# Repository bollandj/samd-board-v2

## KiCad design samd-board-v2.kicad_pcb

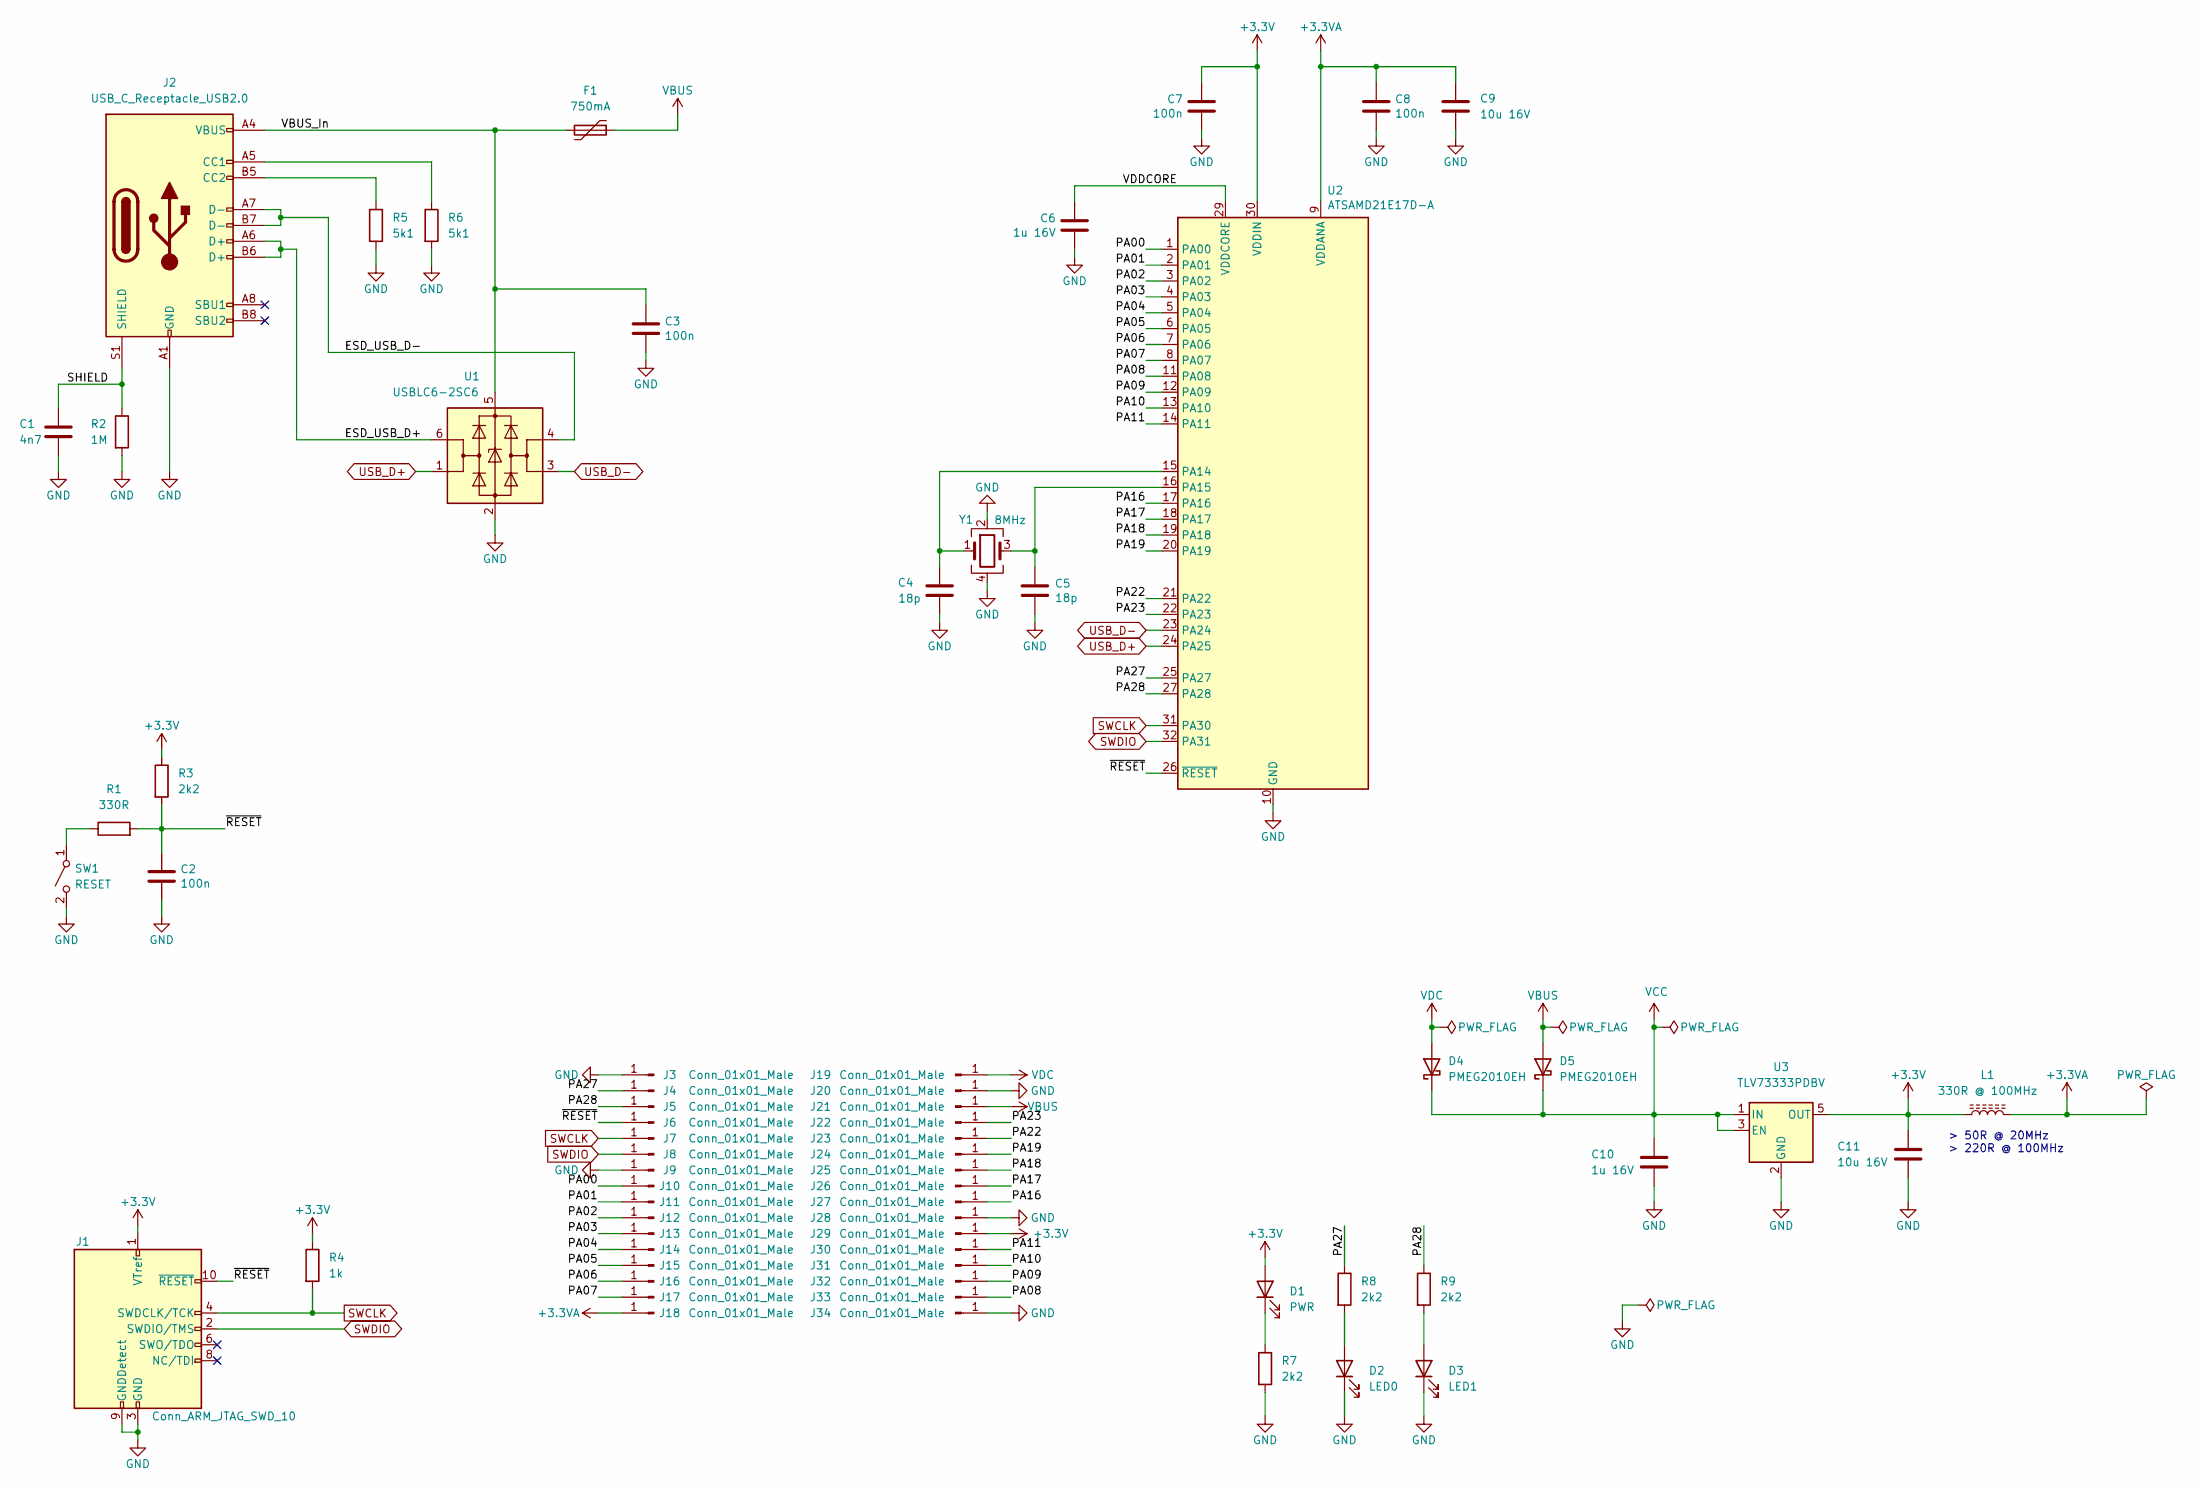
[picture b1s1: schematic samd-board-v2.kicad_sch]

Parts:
C1: 4n7; C_0603_1608Metric
C2, C3, C7, C8: 100n; C_0603_1608Metric; Part CL10B104KB8NNNC
C4, C5: 18p; C_0603_1608Metric
C6, C10: 1u 16V; C_0603_1608Metric; Part CL10B105KO8NNNC
C9, C11: 10u 16V; C_0805_2012Metric; Part CL21B106KOQNNNE
D1: PWR; LED_0603_1608Metric
D2: LED0; LED_0603_1608Metric
D3: LED1; LED_0603_1608Metric
D4, D5: PMEG2010EH; D_SOD-123F; Part PMEG2010EH,115
F1: 750mA; R_1206_3216Metric; Part 1206L075THYR
J1: Conn_ARM_JTAG_SWD_10; PinHeader_2x05_P1.27mm_Vertical
J2: USB_C_Receptacle_USB2.0; USB_C_Receptacle_XKB_U262-16XN-4BVC11; Part U262-161N-4BVC11
J3, J9, J20, J28, J34: Conn_01x01_Male; PinHeader_1x01_P2.54mm_Vertical_Square
J4, J5, J6, J7, J8, J10, J11, J12, J13, J14, J15, J16, J17, J18, J19, J21, J22, J23, J24, J25, J26, J27, J29, J30, J31, J32, J33: Conn_01x01_Male; PinHeader_1x01_P2.54mm_Vertical_Round
L1: 330R @ 100MHz; L_0603_1608Metric
R1: 330R; R_0603_1608Metric
R2: 1M; R_0603_1608Metric
R3, R7, R8, R9: 2k2; R_0603_1608Metric
R4: 1k; R_0603_1608Metric
R5, R6: 5k1; R_0603_1608Metric
SW1: RESET; SW_Push_SPST_NO_Alps_SKRK; Part SKRKAEE020
U1: USBLC6-2SC6; SOT-23-6; Part USBLC6-2SC6
U2: ATSAMD21E17D-A; TQFP-32_7x7mm_P0.8mm; Part ATSAMD21E17D
U3: TLV73333PDBV; SOT-23-5; Part TLV73333PDBVR
Y1: 8MHz; Crystal_SMD_3225-4Pin_3.2x2.5mm

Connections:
+3.3VA: C8.2, C9.1, J18.1, L1.2, U2.9 (VDDANA)
+3V3: C7.2, C11.1, D1.2 (A), J1.1 (VTref), J29.1, L1.1, R3.1, R4.1, U2.30 (VDDIN), U3.5 (OUT)
/ESD_USB_D+: J2.A6 (D+), J2.B6 (D+), U1.6 (I/O1)
/ESD_USB_D-: J2.A7 (D-), J2.B7 (D-), U1.4 (I/O2)
/PA00: J10.1, U2.1 (PA00)
/PA01: J11.1, U2.2 (PA01)
/PA02: J12.1, U2.3 (PA02)
/PA03: J13.1, U2.4 (PA03)
/PA04: J14.1, U2.5 (PA04)
/PA05: J15.1, U2.6 (PA05)
/PA06: J16.1, U2.7 (PA06)
/PA07: J17.1, U2.8 (PA07)
/PA08: J33.1, U2.11 (PA08)
/PA09: J32.1, U2.12 (PA09)
/PA10: J31.1, U2.13 (PA10)
/PA11: J30.1, U2.14 (PA11)
/PA16: J27.1, U2.17 (PA16)
/PA17: J26.1, U2.18 (PA17)
/PA18: J25.1, U2.19 (PA18)
/PA19: J24.1, U2.20 (PA19)
/PA22: J23.1, U2.21 (PA22)
/PA23: J22.1, U2.22 (PA23)
/PA27: J4.1, R8.1, U2.25 (PA27)
/PA28: J5.1, R9.1, U2.27 (PA28)
/SHIELD: C1.1, J2.S1 (SHIELD), R2.1
/VBUS_In: C3.2, F1.2, J2.A4 (VBUS), J2.A9 (VBUS), J2.B4 (VBUS), J2.B9 (VBUS), U1.5 (VBUS)
/VDDCORE: C6.2, U2.29 (VDDCORE)
/~RESET: C2.2, J1.10 (~RESET), J6.1, R1.2, R3.2, U2.26 (~RESET)
GND: C1.2, C2.1, C3.1, C4.2, C5.2, C6.1, C7.1, C8.1, C9.2, C10.2, C11.2, D2.1 (K), D3.1 (K), J1.3 (GND), J1.5 (GND), J1.9 (GNDDetect), J2.A1 (GND), J2.A12 (GND), J2.B1 (GND), J2.B12 (GND), J3.1, J9.1, J20.1, J28.1, J34.1, R2.2, R5.2, R6.2, R7.2, SW1.2 (B), U1.2 (GND), U2.10 (GND), U2.28 (GND), U3.2 (GND), Y1.2, Y1.4
unnamed: C4.1, U2.15 (PA14), Y1.1
unnamed: C5.1, U2.16 (PA15), Y1.3
unnamed: D1.1 (K), R7.1
unnamed: D2.2 (A), R8.2
unnamed: D3.2 (A), R9.2
unnamed: J2.A5 (CC1), R6.1
unnamed: J2.B5 (CC2), R5.1
unnamed: R1.1, SW1.1 (A)
SWCLK: J1.4 (SWDCLK/TCK), J7.1, R4.2, U2.31 (PA30)
SWDIO: J1.2 (SWDIO/TMS), J8.1, U2.32 (PA31)
USB_D+: U1.1 (I/O1), U2.24 (PA25)
USB_D-: U1.3 (I/O2), U2.23 (PA24)
VBUS: D5.2 (A), F1.1, J21.1
VCC: C10.1, D4.1 (K), D5.1 (K), U3.1 (IN), U3.3 (EN)
VDC: D4.2 (A), J19.1

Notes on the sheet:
> 50R @ 20MHz > 220R @ 100MHz

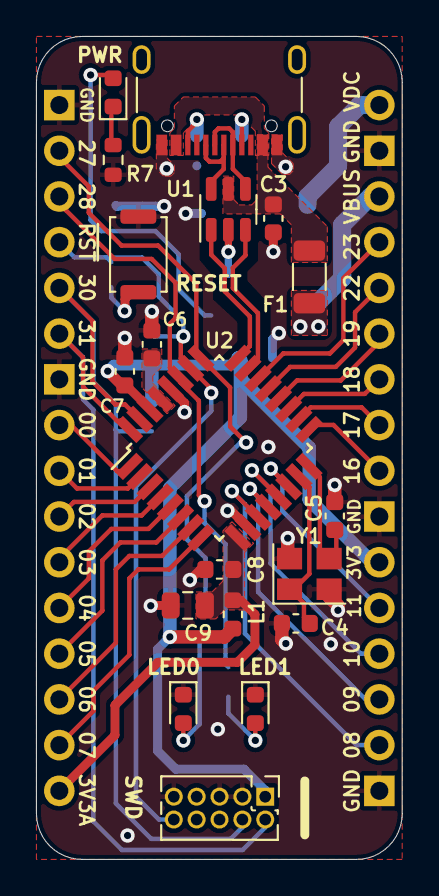
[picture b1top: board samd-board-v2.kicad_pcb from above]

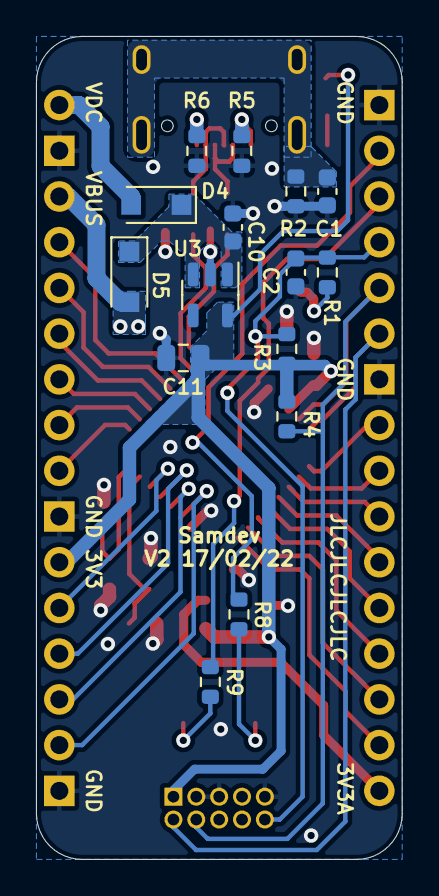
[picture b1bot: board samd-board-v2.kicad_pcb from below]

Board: 4 copper layers, 20.3 x 45.7 mm, 66 parts (47 on the bottom side), 44 nets.
